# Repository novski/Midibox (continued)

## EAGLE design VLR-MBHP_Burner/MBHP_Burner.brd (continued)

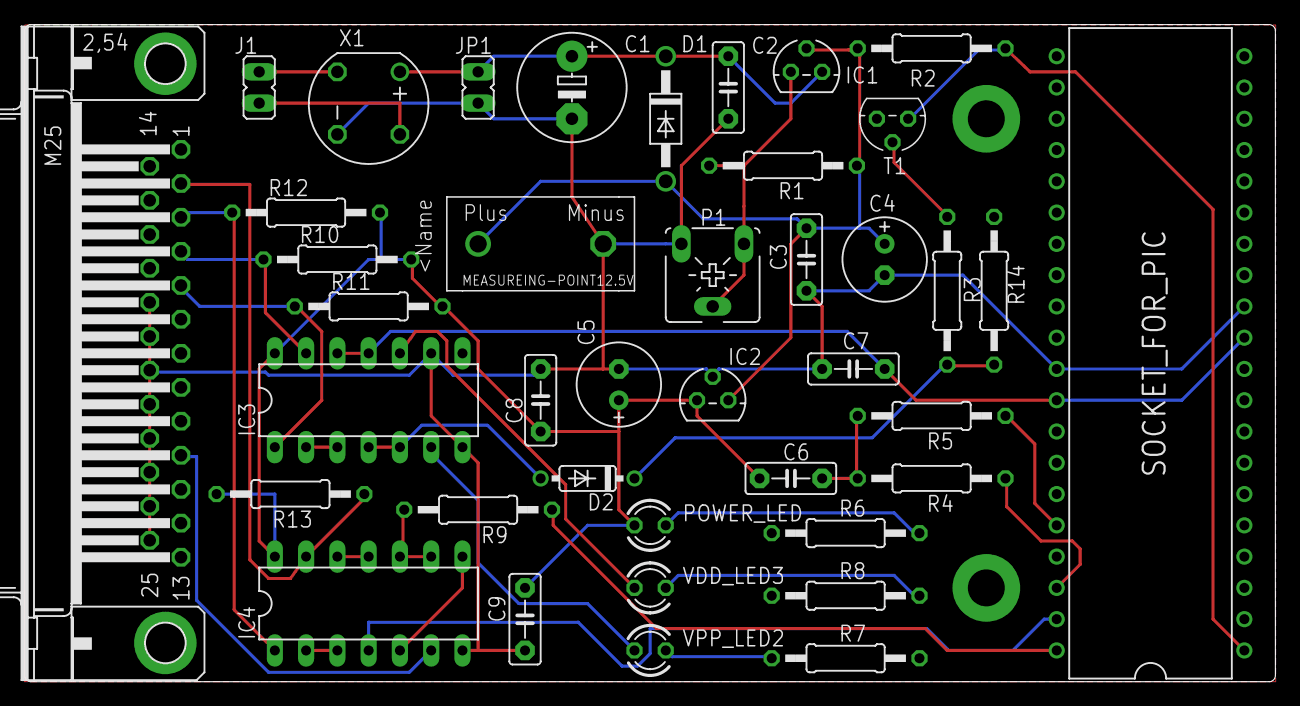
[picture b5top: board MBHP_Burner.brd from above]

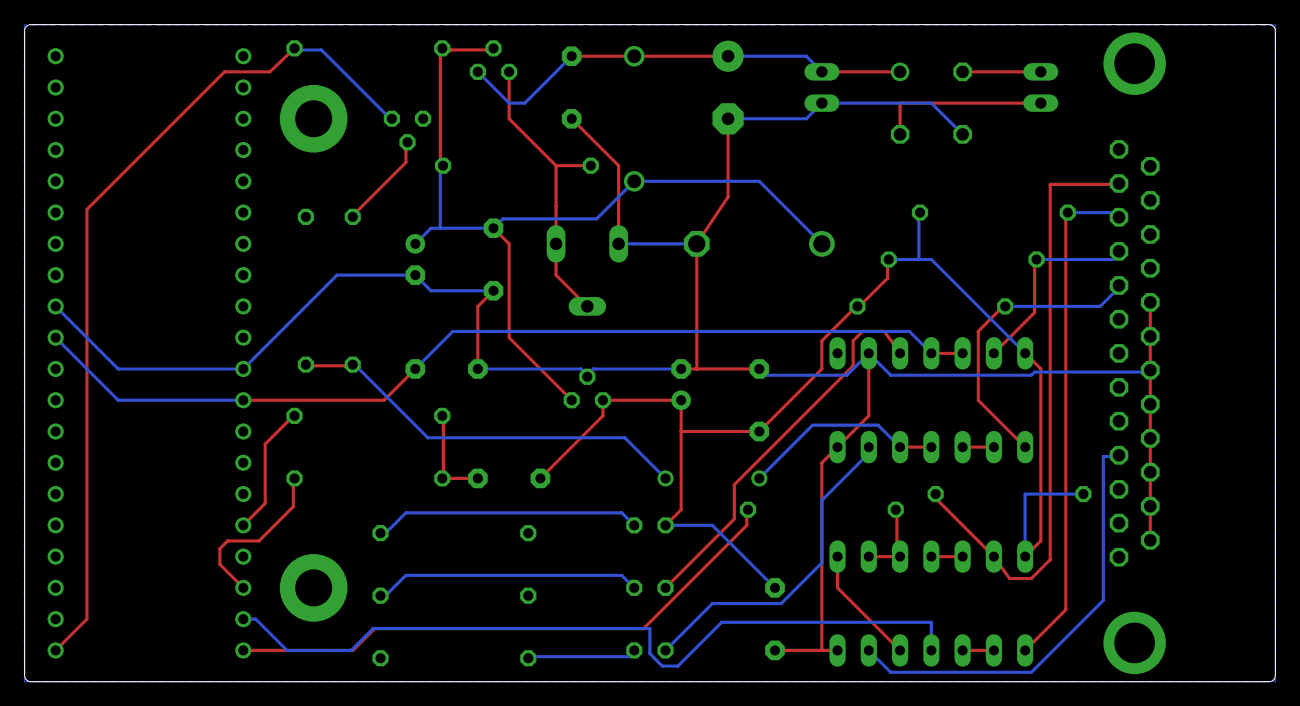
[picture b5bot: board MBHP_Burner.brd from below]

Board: 2 copper layers, 101.6 x 53.4 mm, 47 parts (3 on the bottom side), 31 nets.

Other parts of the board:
U$2, U$3: VLRLAB
U$4: MBHP_BURNER
U$5, U$6: (C)T.KLOSE

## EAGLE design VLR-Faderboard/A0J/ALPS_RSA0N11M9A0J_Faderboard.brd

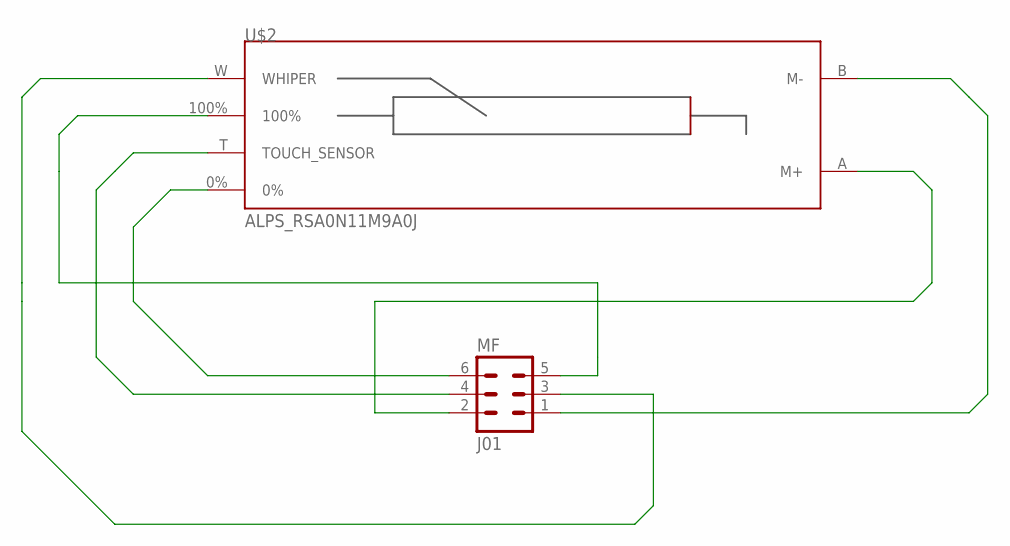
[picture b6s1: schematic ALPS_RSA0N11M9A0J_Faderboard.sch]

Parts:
MF: J01; ML6
U$2: ALPS_RSA0N11M9A0J; ALPS_RAS011M9A0J

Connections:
unnamed: MF.6, U$2.0%
unnamed: MF.2, U$2.A (M+)
unnamed: MF.3, U$2.W (WHIPER)
unnamed: MF.1, U$2.B (M-)
unnamed: MF.4, U$2.T (TOUCH_SENSOR)
unnamed: MF.5, U$2.100%

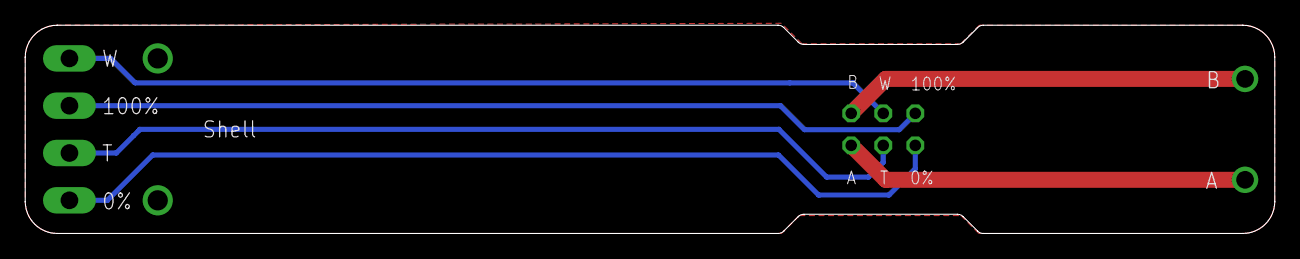
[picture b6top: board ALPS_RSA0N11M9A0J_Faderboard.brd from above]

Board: 2 copper layers, 99.1 x 16.5 mm, 3 parts (1 on the bottom side), 6 nets.

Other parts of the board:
U$1: VLRLAB

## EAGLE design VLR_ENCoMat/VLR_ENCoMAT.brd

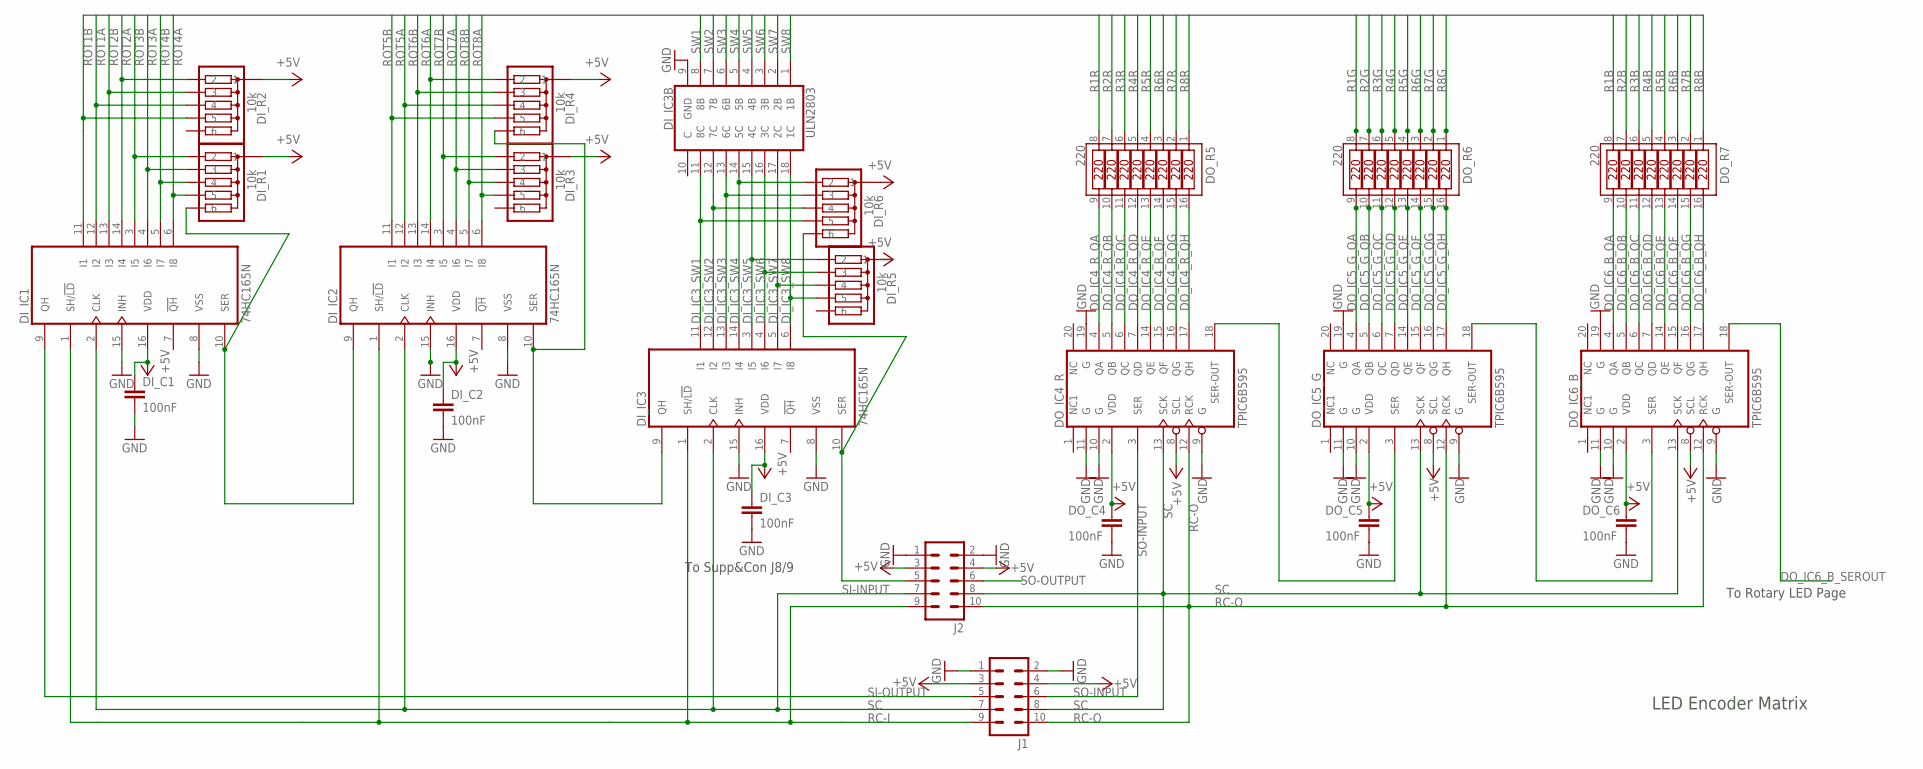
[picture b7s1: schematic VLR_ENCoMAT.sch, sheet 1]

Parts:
DI_C1, DI_C2, DI_C3: 100nF; C025-024X044
DI_IC1, DI_IC2, DI_IC3: 74HC165N; SO16D
DI_IC3B: ULN2803; SO18W
DI_R1, DI_R3, DI_R6: 10k; SIL6-SMD-R
DI_R2, DI_R4, DI_R5: 10k; SIL6-SMD
DO_C4, DO_C5, DO_C6: 100nF; C025-024X044
DO_IC4_R, DO_IC5_G, DO_IC6_B: TPIC6B595; SO20W
DO_R5, DO_R6, DO_R7: 220; SOIC16W
J1, J2: ML10

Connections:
+5V: DI_C1.1, DI_C2.1, DI_C3.1, DI_IC1.16 (VDD), DI_IC2.16 (VDD), DI_IC3.16 (VDD), DI_R1.P$6 (1), DI_R2.P$1 (1), DI_R3.P$6 (1), DI_R4.P$1 (1), DI_R5.P$1 (1), DI_R6.P$6 (1), DO_C4.1, DO_C5.1, DO_C6.1, DO_IC4_R.2 (VDD), DO_IC4_R.8 (SCL), DO_IC5_G.2 (VDD), DO_IC5_G.8 (SCL), DO_IC6_B.2 (VDD), DO_IC6_B.8 (SCL), J1.3, J1.4, J2.3, J2.4; also elsewhere on the board
DI_IC3_SW1: DI_IC3.11 (I1), DI_IC3B.11 (8C), DI_R6.P$2 (5)
DI_IC3_SW2: DI_IC3.12 (I2), DI_IC3B.12 (7C), DI_R6.P$3 (4)
DI_IC3_SW3: DI_IC3.13 (I3), DI_IC3B.13 (6C), DI_R6.P$4 (3)
DI_IC3_SW4: DI_IC3.14 (I4), DI_IC3B.14 (5C), DI_R6.P$5 (2)
DI_IC3_SW5: DI_IC3.3 (I5), DI_IC3B.15 (4C), DI_R5.P$2 (2)
DI_IC3_SW6: DI_IC3.4 (I6), DI_IC3B.16 (3C), DI_R5.P$3 (3)
DI_IC3_SW7: DI_IC3.5 (I7), DI_IC3B.17 (2C), DI_R5.P$4 (4)
DI_IC3_SW8: DI_IC3.6 (I8), DI_IC3B.18 (1C), DI_R5.P$5 (5)
DI_IC4_SER_OUT2: DI_IC1.10 (SER), DI_IC2.9 (QH), DI_R1.P$1 (6)
DI_IC5_SER_OUT2: DI_IC2.10 (SER), DI_IC3.9 (QH), DI_R4.P$6 (6)
DO_IC4_R_QA: DO_IC4_R.4 (QA), DO_R5.9
DO_IC4_R_QB: DO_IC4_R.5 (QB), DO_R5.10
DO_IC4_R_QC: DO_IC4_R.6 (QC), DO_R5.11
DO_IC4_R_QD: DO_IC4_R.7 (QD), DO_R5.12
DO_IC4_R_QE: DO_IC4_R.14 (QE), DO_R5.13
DO_IC4_R_QF: DO_IC4_R.15 (QF), DO_R5.14
DO_IC4_R_QG: DO_IC4_R.16 (QG), DO_R5.15
DO_IC4_R_QH: DO_IC4_R.17 (QH), DO_R5.16
DO_IC4_R_SEROUT: DO_IC4_R.18 (SER-OUT), DO_IC5_G.3 (SER)
DO_IC5_G_QA: DO_IC5_G.4 (QA), DO_R6.9
DO_IC5_G_QB: DO_IC5_G.5 (QB), DO_R6.10
DO_IC5_G_QC: DO_IC5_G.6 (QC), DO_R6.11
DO_IC5_G_QD: DO_IC5_G.7 (QD), DO_R6.12
DO_IC5_G_QE: DO_IC5_G.14 (QE), DO_R6.13
DO_IC5_G_QF: DO_IC5_G.15 (QF), DO_R6.14
DO_IC5_G_QG: DO_IC5_G.16 (QG), DO_R6.15
DO_IC5_G_QH: DO_IC5_G.17 (QH), DO_R6.16
DO_IC5_G_SEROUT: DO_IC5_G.18 (SER-OUT), DO_IC6_B.3 (SER)
DO_IC6_B_QA: DO_IC6_B.4 (QA), DO_R7.9
DO_IC6_B_QB: DO_IC6_B.5 (QB), DO_R7.10
DO_IC6_B_QC: DO_IC6_B.6 (QC), DO_R7.11
DO_IC6_B_QD: DO_IC6_B.7 (QD), DO_R7.12
DO_IC6_B_QE: DO_IC6_B.14 (QE), DO_R7.13
DO_IC6_B_QF: DO_IC6_B.15 (QF), DO_R7.14
DO_IC6_B_QG: DO_IC6_B.16 (QG), DO_R7.15
DO_IC6_B_QH: DO_IC6_B.17 (QH), DO_R7.16
DO_IC6_B_SEROUT: DO_IC6_B.18 (SER-OUT); also elsewhere on the board
GND: DI_C1.2, DI_C2.2, DI_C3.2, DI_IC1.8 (VSS), DI_IC1.15 (INH), DI_IC2.8 (VSS), DI_IC2.15 (INH), DI_IC3.8 (VSS), DI_IC3.15 (INH), DI_IC3B.9 (GND), DO_C4.2, DO_C5.2, DO_C6.2, DO_IC4_R.9 (G), DO_IC4_R.10 (G), DO_IC4_R.11 (G), DO_IC4_R.19 (G), DO_IC5_G.9 (G), DO_IC5_G.10 (G), DO_IC5_G.11 (G), DO_IC5_G.19 (G), DO_IC6_B.9 (G), DO_IC6_B.10 (G), DO_IC6_B.11 (G), DO_IC6_B.19 (G), J1.1, J1.2, J2.1, J2.2; also elsewhere on the board
R1B: DO_R7.8; also elsewhere on the board
R1G: DO_R6.8; also elsewhere on the board
R1R: DO_R5.8; also elsewhere on the board
R2B: DO_R7.7; also elsewhere on the board
R2G: DO_R6.7; also elsewhere on the board
R2R: DO_R5.7; also elsewhere on the board
R3B: DO_R7.6; also elsewhere on the board
R3G: DO_R6.6; also elsewhere on the board
R3R: DO_R5.6; also elsewhere on the board
R4B: DO_R7.5; also elsewhere on the board
R4G: DO_R6.5; also elsewhere on the board
R4R: DO_R5.5; also elsewhere on the board
R5B: DO_R7.4; also elsewhere on the board
R5G: DO_R6.4; also elsewhere on the board
R5R: DO_R5.4; also elsewhere on the board
R6B: DO_R7.3; also elsewhere on the board
R6G: DO_R6.3; also elsewhere on the board
R6R: DO_R5.3; also elsewhere on the board
R7B: DO_R7.2; also elsewhere on the board
R7G: DO_R6.2; also elsewhere on the board
R7R: DO_R5.2; also elsewhere on the board
R8B: DO_R7.1; also elsewhere on the board
R8G: DO_R6.1; also elsewhere on the board
R8R: DO_R5.1; also elsewhere on the board
RC-I: DI_IC1.1 (SH/!LD), DI_IC2.1 (SH/!LD), DI_IC3.1 (SH/!LD), J1.9, J2.9
RC-O: DO_IC4_R.12 (RCK), DO_IC5_G.12 (RCK), DO_IC6_B.12 (RCK), J1.10, J2.10; also elsewhere on the board
ROT1A: DI_IC1.12 (I2), DI_R2.P$4 (4); also elsewhere on the board
ROT1B: DI_IC1.11 (I1), DI_R2.P$5 (5); also elsewhere on the board
ROT2A: DI_IC1.14 (I4), DI_R2.P$2 (2); also elsewhere on the board
ROT2B: DI_IC1.13 (I3), DI_R2.P$3 (3); also elsewhere on the board
ROT3A: DI_IC1.4 (I6), DI_R1.P$4 (3); also elsewhere on the board
ROT3B: DI_IC1.3 (I5), DI_R1.P$5 (2); also elsewhere on the board
ROT4A: DI_IC1.6 (I8), DI_R1.P$2 (5); also elsewhere on the board
ROT4B: DI_IC1.5 (I7), DI_R1.P$3 (4); also elsewhere on the board
ROT5A: DI_IC2.12 (I2), DI_R4.P$4 (4); also elsewhere on the board
ROT5B: DI_IC2.11 (I1), DI_R4.P$5 (5); also elsewhere on the board
ROT6A: DI_IC2.14 (I4), DI_R4.P$2 (2); also elsewhere on the board
ROT6B: DI_IC2.13 (I3), DI_R4.P$3 (3); also elsewhere on the board
ROT7A: DI_IC2.4 (I6), DI_R3.P$4 (3); also elsewhere on the board
ROT7B: DI_IC2.3 (I5), DI_R3.P$5 (2); also elsewhere on the board
ROT8A: DI_IC2.6 (I8), DI_R3.P$2 (5); also elsewhere on the board
ROT8B: DI_IC2.5 (I7), DI_R3.P$3 (4); also elsewhere on the board
SC: DI_IC1.2 (CLK), DI_IC2.2 (CLK), DI_IC3.2 (CLK), DO_IC4_R.13 (SCK), DO_IC5_G.13 (SCK), DO_IC6_B.13 (SCK), J1.7, J1.8, J2.7, J2.8; also elsewhere on the board
SI-INPUT: DI_IC3.10 (SER), DI_R6.P$1 (6), J2.5
SI-OUTPUT: DI_IC1.9 (QH), J1.5
SO-INPUT: DO_IC4_R.3 (SER), J1.6
SO-OUTPUT: J2.6; also elsewhere on the board
SW1: DI_IC3B.8 (8B); also elsewhere on the board
SW2: DI_IC3B.7 (7B); also elsewhere on the board
SW3: DI_IC3B.6 (6B); also elsewhere on the board
SW4: DI_IC3B.5 (5B); also elsewhere on the board
SW5: DI_IC3B.4 (4B); also elsewhere on the board
SW6: DI_IC3B.3 (3B); also elsewhere on the board
SW7: DI_IC3B.2 (2B); also elsewhere on the board
SW8: DI_IC3B.1 (1B); also elsewhere on the board

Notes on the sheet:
LED Encoder Matrix
To Supp&Con J8/9
To Rotary LED Page

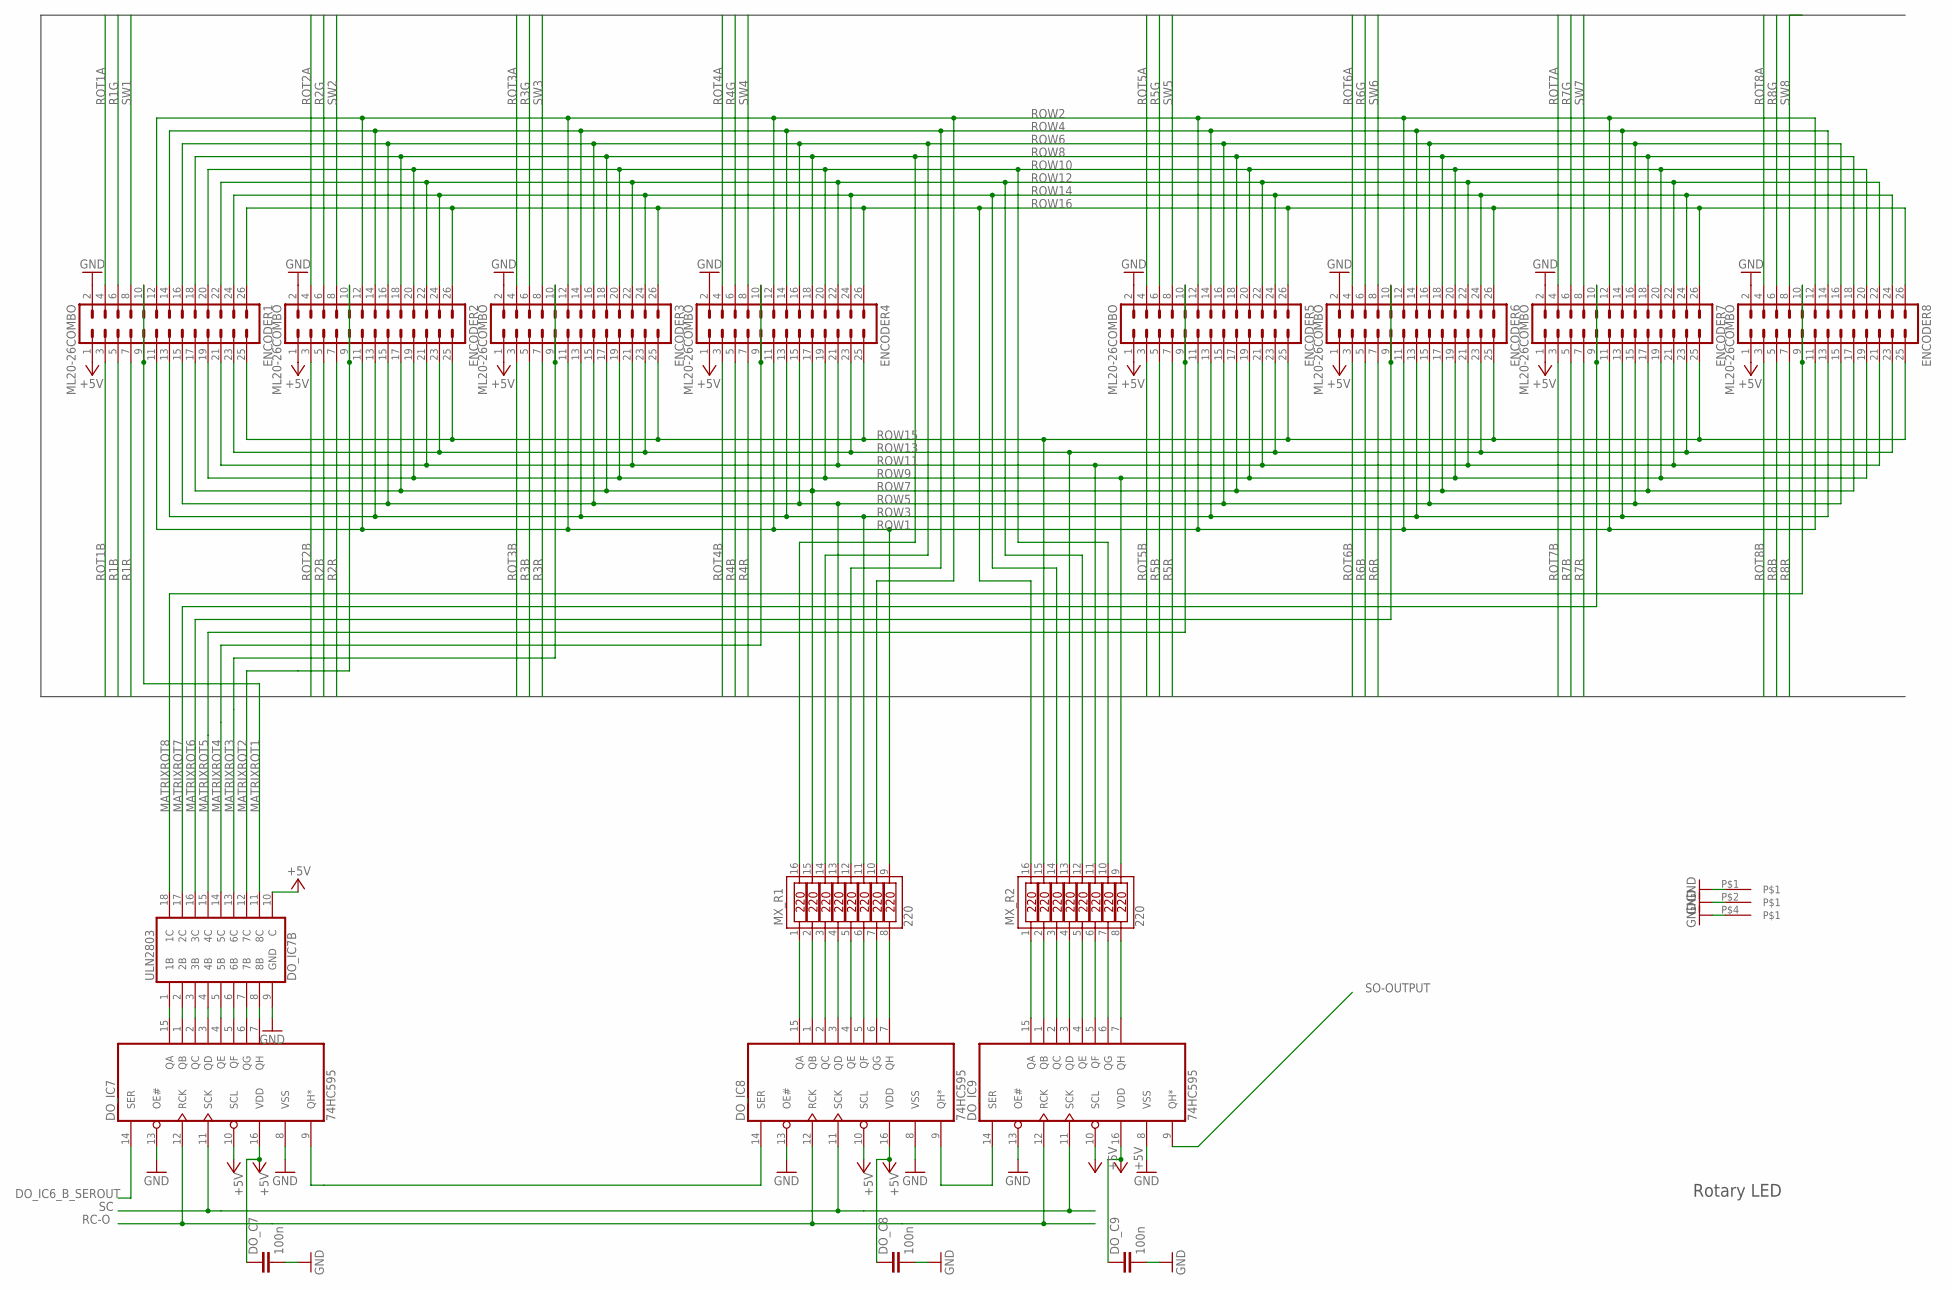
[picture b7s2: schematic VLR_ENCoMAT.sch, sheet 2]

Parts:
DO_C7, DO_C8, DO_C9: 100n; C025-024X044
DO_IC7, DO_IC8, DO_IC9: 74HC595; SO16D
DO_IC7B: ULN2803; SO18W
ENCODER1, ENCODER2, ENCODER3, ENCODER4, ENCODER5, ENCODER6, ENCODER7, ENCODER8: ML20-26COMBO
MX_R1, MX_R2: 220; SOIC16W
U$2: MIDIBOX_HALF; MIDIBOX14X6

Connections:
+5V: DO_C7.1, DO_C8.1, DO_C9.1, DO_IC7.10 (SCL), DO_IC7.16 (VDD), DO_IC7B.10 (C), DO_IC8.10 (SCL), DO_IC8.16 (VDD), DO_IC9.10 (SCL), DO_IC9.16 (VDD), ENCODER1.1, ENCODER2.1, ENCODER3.1, ENCODER4.1, ENCODER5.1, ENCODER6.1, ENCODER7.1, ENCODER8.1; also elsewhere on the board
DO_IC6_B_SEROUT: DO_IC7.14 (SER); also elsewhere on the board
DO_IC7_QA: DO_IC7.15 (QA), DO_IC7B.1 (1B)
DO_IC7_QB: DO_IC7.1 (QB), DO_IC7B.2 (2B)
DO_IC7_QC: DO_IC7.2 (QC), DO_IC7B.3 (3B)
DO_IC7_QD: DO_IC7.3 (QD), DO_IC7B.4 (4B)
DO_IC7_QE: DO_IC7.4 (QE), DO_IC7B.5 (5B)
DO_IC7_QF: DO_IC7.5 (QF), DO_IC7B.6 (6B)
DO_IC7_QG: DO_IC7.6 (QG), DO_IC7B.7 (7B)
DO_IC7_QH: DO_IC7.7 (QH), DO_IC7B.8 (8B)
DO_IC7_SEROUT: DO_IC7.9 (QH*), DO_IC8.14 (SER)
DO_IC8_ROW1: DO_IC8.7 (QH), MX_R1.8
DO_IC8_ROW2: DO_IC8.6 (QG), MX_R1.7
DO_IC8_ROW3: DO_IC8.5 (QF), MX_R1.6
DO_IC8_ROW4: DO_IC8.4 (QE), MX_R1.5
DO_IC8_ROW5: DO_IC8.3 (QD), MX_R1.4
DO_IC8_ROW6: DO_IC8.2 (QC), MX_R1.3
DO_IC8_ROW7: DO_IC8.1 (QB), MX_R1.2
DO_IC8_ROW8: DO_IC8.15 (QA), MX_R1.1
DO_IC8_SEROUT: DO_IC8.9 (QH*), DO_IC9.14 (SER)
DO_IC9_ROW1: DO_IC9.7 (QH), MX_R2.8
DO_IC9_ROW2: DO_IC9.6 (QG), MX_R2.7
DO_IC9_ROW3: DO_IC9.5 (QF), MX_R2.6
DO_IC9_ROW4: DO_IC9.4 (QE), MX_R2.5
DO_IC9_ROW5: DO_IC9.3 (QD), MX_R2.4
DO_IC9_ROW6: DO_IC9.2 (QC), MX_R2.3
DO_IC9_ROW7: DO_IC9.1 (QB), MX_R2.2
DO_IC9_ROW8: DO_IC9.15 (QA), MX_R2.1
GND: DO_C7.2, DO_C8.2, DO_C9.2, DO_IC7.8 (VSS), DO_IC7.13 (OE#), DO_IC7B.9 (GND), DO_IC8.8 (VSS), DO_IC8.13 (OE#), DO_IC9.8 (VSS), DO_IC9.13 (OE#), ENCODER1.2, ENCODER2.2, ENCODER3.2, ENCODER4.2, ENCODER5.2, ENCODER6.2, ENCODER7.2, ENCODER8.2, U$2.P$1, U$2.P$2, U$2.P$4; also elsewhere on the board
MATRIXROT1: DO_IC7B.11 (8C), ENCODER1.9, ENCODER1.10
MATRIXROT2: DO_IC7B.12 (7C), ENCODER2.9, ENCODER2.10
MATRIXROT3: DO_IC7B.13 (6C), ENCODER3.9, ENCODER3.10
MATRIXROT4: DO_IC7B.14 (5C), ENCODER4.9, ENCODER4.10
MATRIXROT5: DO_IC7B.15 (4C), ENCODER5.9, ENCODER5.10
MATRIXROT6: DO_IC7B.16 (3C), ENCODER6.9, ENCODER6.10
MATRIXROT7: DO_IC7B.17 (2C), ENCODER7.9, ENCODER7.10
MATRIXROT8: DO_IC7B.18 (1C), ENCODER8.9, ENCODER8.10
R1B: ENCODER1.5; also elsewhere on the board
R1G: ENCODER1.6; also elsewhere on the board
R1R: ENCODER1.7; also elsewhere on the board
R2B: ENCODER2.5; also elsewhere on the board
R2G: ENCODER2.6; also elsewhere on the board
R2R: ENCODER2.7; also elsewhere on the board
R3B: ENCODER3.5; also elsewhere on the board
R3G: ENCODER3.6; also elsewhere on the board
R3R: ENCODER3.7; also elsewhere on the board
R4B: ENCODER4.5; also elsewhere on the board
R4G: ENCODER4.6; also elsewhere on the board
R4R: ENCODER4.7; also elsewhere on the board
R5B: ENCODER5.5; also elsewhere on the board
R5G: ENCODER5.6; also elsewhere on the board
R5R: ENCODER5.7; also elsewhere on the board
R6B: ENCODER6.5; also elsewhere on the board
R6G: ENCODER6.6; also elsewhere on the board
R6R: ENCODER6.7; also elsewhere on the board
R7B: ENCODER7.5; also elsewhere on the board
R7G: ENCODER7.6; also elsewhere on the board
R7R: ENCODER7.7; also elsewhere on the board
R8B: ENCODER8.5; also elsewhere on the board
R8G: ENCODER8.6; also elsewhere on the board
R8R: ENCODER8.7; also elsewhere on the board
RC-O: DO_IC7.12 (RCK), DO_IC8.12 (RCK), DO_IC9.12 (RCK); also elsewhere on the board
ROT1A: ENCODER1.4; also elsewhere on the board
ROT1B: ENCODER1.3; also elsewhere on the board
ROT2A: ENCODER2.4; also elsewhere on the board
ROT2B: ENCODER2.3; also elsewhere on the board
ROT3A: ENCODER3.4; also elsewhere on the board
ROT3B: ENCODER3.3; also elsewhere on the board
ROT4A: ENCODER4.4; also elsewhere on the board
ROT4B: ENCODER4.3; also elsewhere on the board
ROT5A: ENCODER5.4; also elsewhere on the board
ROT5B: ENCODER5.3; also elsewhere on the board
ROT6A: ENCODER6.4; also elsewhere on the board
ROT6B: ENCODER6.3; also elsewhere on the board
ROT7A: ENCODER7.4; also elsewhere on the board
ROT7B: ENCODER7.3; also elsewhere on the board
ROT8A: ENCODER8.4; also elsewhere on the board
ROT8B: ENCODER8.3; also elsewhere on the board
ROW1: ENCODER1.11, ENCODER2.11, ENCODER3.11, ENCODER4.11, ENCODER5.11, ENCODER6.11, ENCODER7.11, ENCODER8.11, MX_R1.9
ROW2: ENCODER1.12, ENCODER2.12, ENCODER3.12, ENCODER4.12, ENCODER5.12, ENCODER6.12, ENCODER7.12, ENCODER8.12, MX_R1.10
ROW3: ENCODER1.13, ENCODER2.13, ENCODER3.13, ENCODER4.13, ENCODER5.13, ENCODER6.13, ENCODER7.13, ENCODER8.13, MX_R1.11
ROW4: ENCODER1.14, ENCODER2.14, ENCODER3.14, ENCODER4.14, ENCODER5.14, ENCODER6.14, ENCODER7.14, ENCODER8.14, MX_R1.12
ROW5: ENCODER1.15, ENCODER2.15, ENCODER3.15, ENCODER4.15, ENCODER5.15, ENCODER6.15, ENCODER7.15, ENCODER8.15, MX_R1.13
ROW6: ENCODER1.16, ENCODER2.16, ENCODER3.16, ENCODER4.16, ENCODER5.16, ENCODER6.16, ENCODER7.16, ENCODER8.16, MX_R1.14
ROW7: ENCODER1.17, ENCODER2.17, ENCODER3.17, ENCODER4.17, ENCODER5.17, ENCODER6.17, ENCODER7.17, ENCODER8.17, MX_R1.15
ROW8: ENCODER1.18, ENCODER2.18, ENCODER3.18, ENCODER4.18, ENCODER5.18, ENCODER6.18, ENCODER7.18, ENCODER8.18, MX_R1.16
ROW9: ENCODER1.19, ENCODER2.19, ENCODER3.19, ENCODER4.19, ENCODER5.19, ENCODER6.19, ENCODER7.19, ENCODER8.19, MX_R2.9
ROW10: ENCODER1.20, ENCODER2.20, ENCODER3.20, ENCODER4.20, ENCODER5.20, ENCODER6.20, ENCODER7.20, ENCODER8.20, MX_R2.10
ROW11: ENCODER1.21, ENCODER2.21, ENCODER3.21, ENCODER4.21, ENCODER5.21, ENCODER6.21, ENCODER7.21, ENCODER8.21, MX_R2.11
ROW12: ENCODER1.22, ENCODER2.22, ENCODER3.22, ENCODER4.22, ENCODER5.22, ENCODER6.22, ENCODER7.22, ENCODER8.22, MX_R2.12
ROW13: ENCODER1.23, ENCODER2.23, ENCODER3.23, ENCODER4.23, ENCODER5.23, ENCODER6.23, ENCODER7.23, ENCODER8.23, MX_R2.13
ROW14: ENCODER1.24, ENCODER2.24, ENCODER3.24, ENCODER4.24, ENCODER5.24, ENCODER6.24, ENCODER7.24, ENCODER8.24, MX_R2.14
ROW15: ENCODER1.25, ENCODER2.25, ENCODER3.25, ENCODER4.25, ENCODER5.25, ENCODER6.25, ENCODER7.25, ENCODER8.25, MX_R2.15
ROW16: ENCODER1.26, ENCODER2.26, ENCODER3.26, ENCODER4.26, ENCODER5.26, ENCODER6.26, ENCODER7.26, ENCODER8.26, MX_R2.16
SC: DO_IC7.11 (SCK), DO_IC8.11 (SCK), DO_IC9.11 (SCK); also elsewhere on the board
SO-OUTPUT: DO_IC9.9 (QH*); also elsewhere on the board
SW1: ENCODER1.8; also elsewhere on the board
SW2: ENCODER2.8; also elsewhere on the board
SW3: ENCODER3.8; also elsewhere on the board
SW4: ENCODER4.8; also elsewhere on the board
SW5: ENCODER5.8; also elsewhere on the board
SW6: ENCODER6.8; also elsewhere on the board
SW7: ENCODER7.8; also elsewhere on the board
SW8: ENCODER8.8; also elsewhere on the board

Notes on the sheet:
Rotary LED

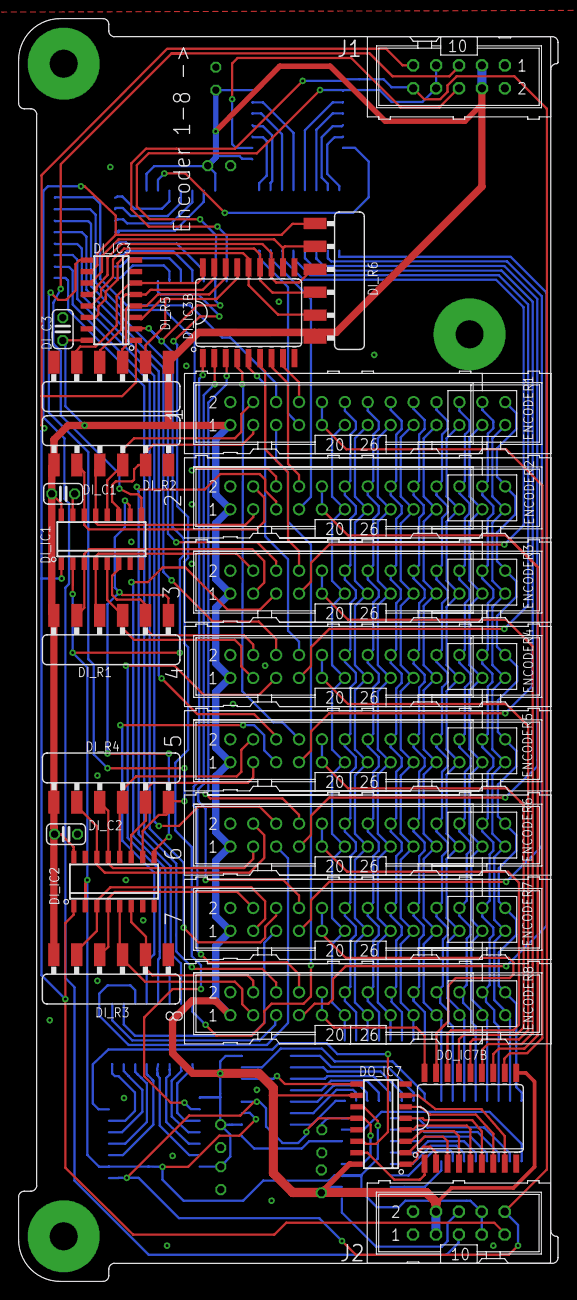
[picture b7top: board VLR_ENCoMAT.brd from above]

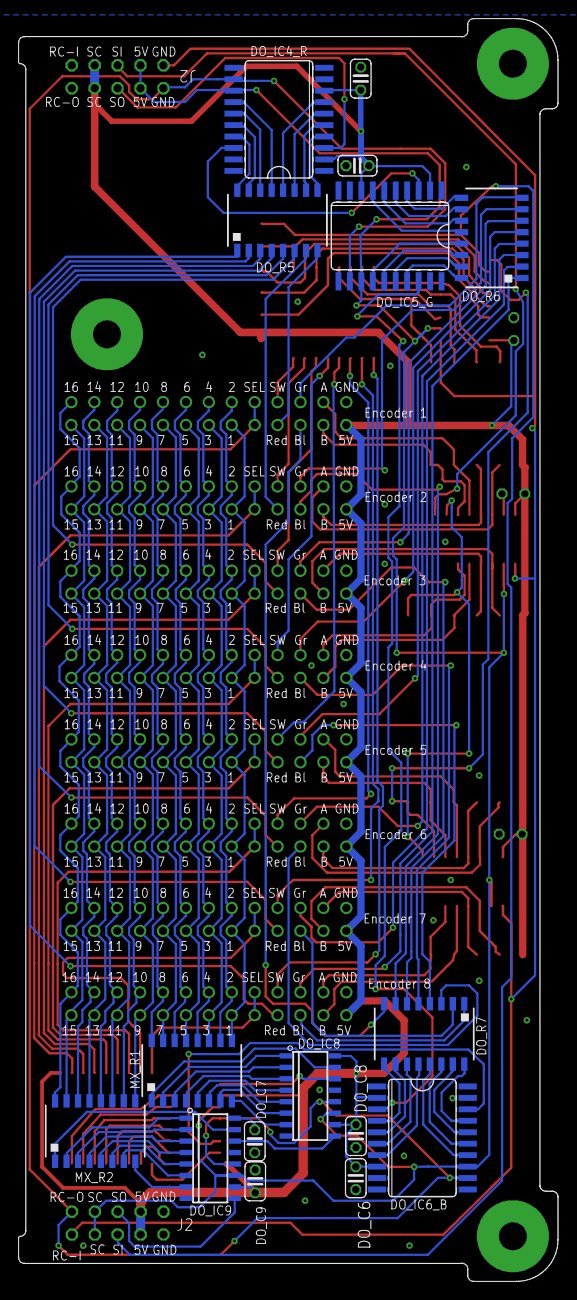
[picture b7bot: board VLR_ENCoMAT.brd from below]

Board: 2 copper layers, 59.8 x 140.0 mm, 45 parts (17 on the bottom side), 144 nets.

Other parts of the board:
U$3: ENCOMAT
U$4, U$5: VLRLAB

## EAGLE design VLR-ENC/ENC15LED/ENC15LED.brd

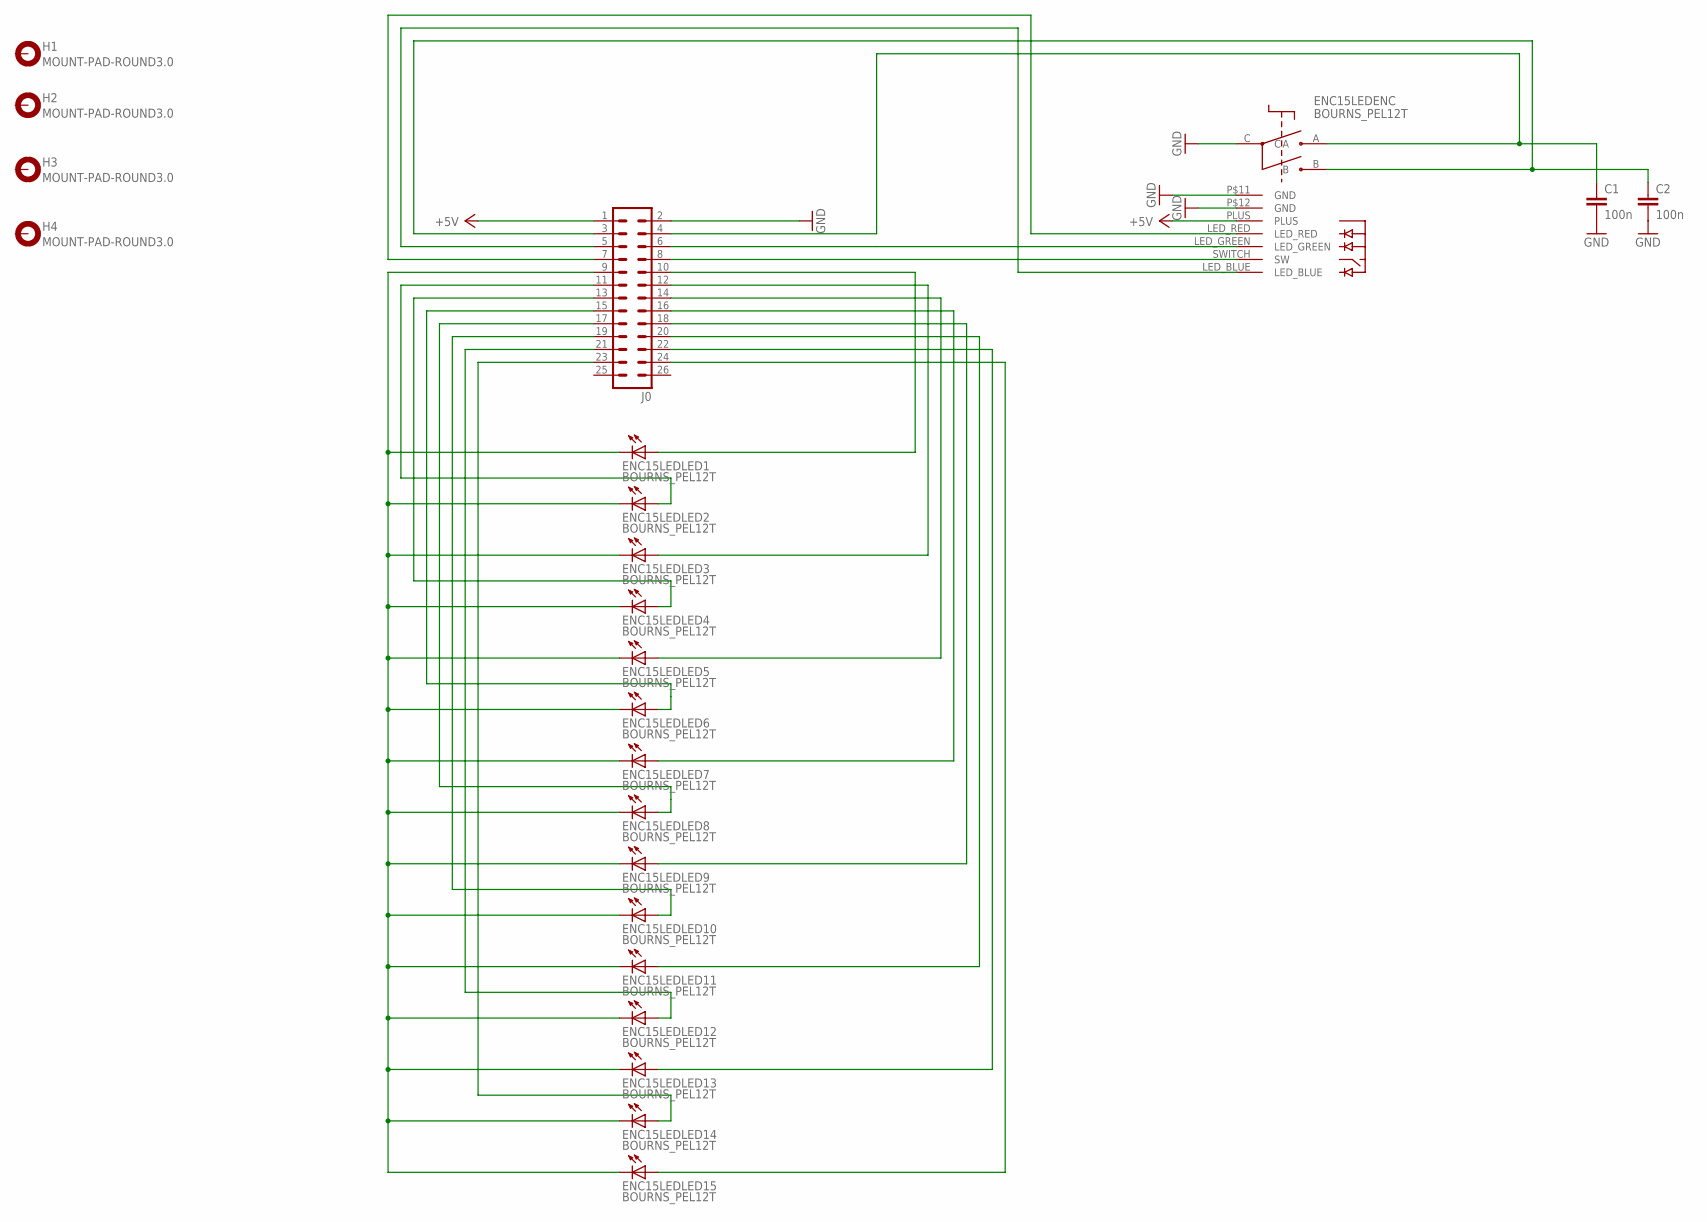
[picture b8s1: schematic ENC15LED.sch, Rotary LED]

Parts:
C1, C2: 100n; C025-025X050
ENC15LED: BOURNS_PEL12T; PEL12T_15LED-RING
H1, H2, H3, H4: MOUNT-PAD-ROUND3.0; 3,0-PAD
J0: ML26

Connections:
+5V: ENC15LED.PLUS, J0.1
BLUE: ENC15LED.LED_BLUE, J0.5
GND: C1.2, C2.2, ENC15LED.C, ENC15LED.P$11 (GND), ENC15LED.P$12 (GND), J0.2
GREEN: ENC15LED.LED_GREEN, J0.6
unnamed: ENC15LED.A01 (A), J0.10
unnamed: ENC15LED.A02 (A), J0.11
unnamed: ENC15LED.A03 (A), J0.12
unnamed: ENC15LED.A04 (A), J0.13
unnamed: ENC15LED.A05 (A), J0.14
unnamed: ENC15LED.A06 (A), J0.15
unnamed: ENC15LED.K01 (C), ENC15LED.K02 (C), ENC15LED.K03 (C), ENC15LED.K04 (C), ENC15LED.K05 (C), ENC15LED.K06 (C), ENC15LED.K07 (C), ENC15LED.K08 (C), ENC15LED.K09 (C), ENC15LED.K10 (C), ENC15LED.K11 (C), ENC15LED.K12 (C), ENC15LED.K13 (C), ENC15LED.K14 (C), ENC15LED.K15 (C), J0.9
unnamed: ENC15LED.A07 (A), J0.16
unnamed: ENC15LED.A08 (A), J0.17
unnamed: ENC15LED.A09 (A), J0.18
unnamed: ENC15LED.A10 (A), J0.19
unnamed: ENC15LED.A11 (A), J0.20
unnamed: ENC15LED.A12 (A), J0.21
unnamed: ENC15LED.A13 (A), J0.22
unnamed: ENC15LED.A14 (A), J0.23
unnamed: ENC15LED.A15 (A), J0.24
PIN_A: C1.1, ENC15LED.A, J0.4
PIN_B: C2.1, ENC15LED.B, J0.3
RED: ENC15LED.LED_RED, J0.7
SWITCH: ENC15LED.SWITCH (SW), J0.8

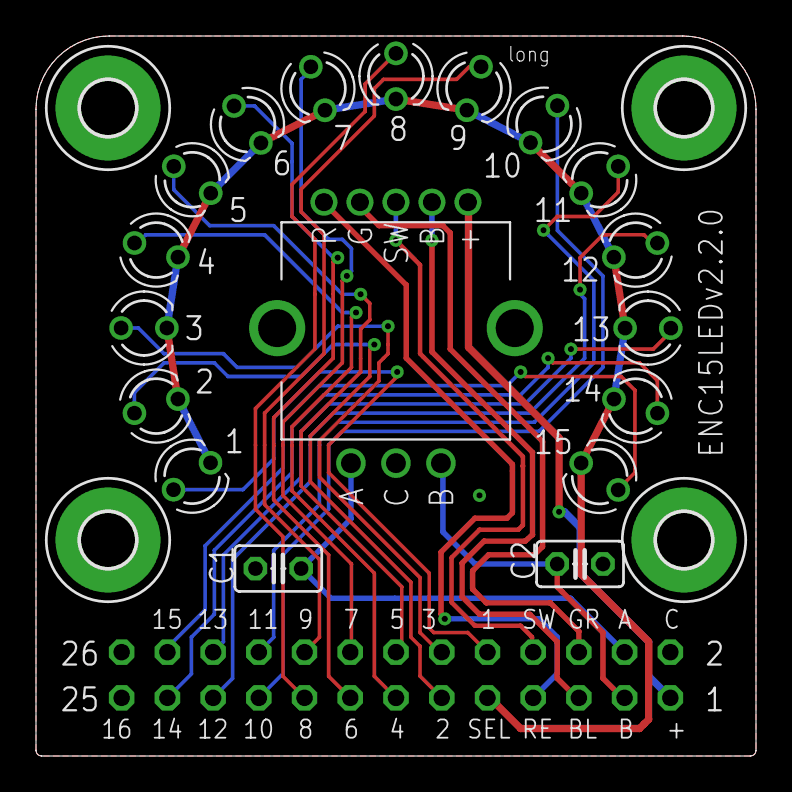
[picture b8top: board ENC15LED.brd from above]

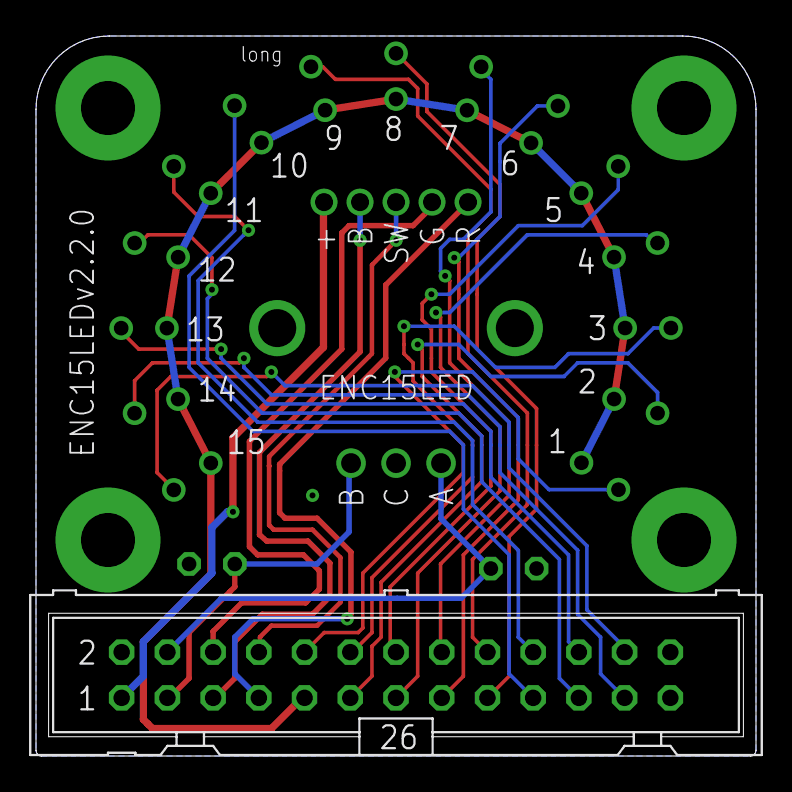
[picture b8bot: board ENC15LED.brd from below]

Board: 2 copper layers, 40.0 x 40.0 mm, 10 parts (2 on the bottom side), 24 nets.

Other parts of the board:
U$1, U$2: VLRLAB_SMAL

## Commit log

2014-05-25 First add.
2014-05-25 Create README.md
    the source of this work is to find at www.ucapps.com
2014-06-07 Added Drawings and Library
2014-06-09 added License
2014-06-29 Added VLR-Enc as new Part
2014-07-01 Add of Core STM32F4Disco
    Midibox Layout for STM32F4Disco unrouted yet…
2014-07-01 Added Eagle Library
    Board Dimension outline
2014-10-31 div. changes
2014-11-13 Untested
    New Layout untested. Prototype in production.
2015-01-18 D IN/OUT changes
    Didn’t get it to a second prototype jet but because of the changes
    related to the first prototype im quite shure this works.
2016-09-10 update to 3x8But
    V1.3.6
2016-09-10 Initial Commit of 8ButV1.2
2016-09-10 update 8EncV1.3.3
    nothing changed just changeing filename to be ready for changes in
    future.
2016-09-10 new rised meterboard V1.4.1
2016-09-10 VLRlab Boardoutlines
2016-09-10 Add ButoMat and butV1
2016-09-10 add ButoMatV1.1.0
2016-09-10 compliant changes v.1.1.2
2016-09-10 comliant changes v1.3
2016-09-10 new EncV1.0.1
2016-09-10 new Enc11LEDv2.0.7
2016-09-10 new Enc15LEDv2.2.0
2016-09-10 new EncoMATv.2.2.1
2016-09-10 new Faderboard and A0Jv1.3
2016-09-10 new A04v.2.0
2016-09-10 new FrontplatteV20.0
2016-09-10 new BurnerV1.1
2016-09-10 new MidiDRVv.1.1.1
2016-09-10 new MidiIO unknown state!
2016-09-10 compliance update v1.5
2016-09-10 compliance update 8oDispV1.3
2016-11-01 added eagle board outlines .brd & .sch
2016-11-01 Add. PDF of schematic
    schema of VLR-MF_NG Motorfader Driver.
    Source: ucapps.de / midibox.org
2018-01-14 add schematic as PDF
